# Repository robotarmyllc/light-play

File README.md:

# light-play
All files related to the Light Play (2013) delta robot project.

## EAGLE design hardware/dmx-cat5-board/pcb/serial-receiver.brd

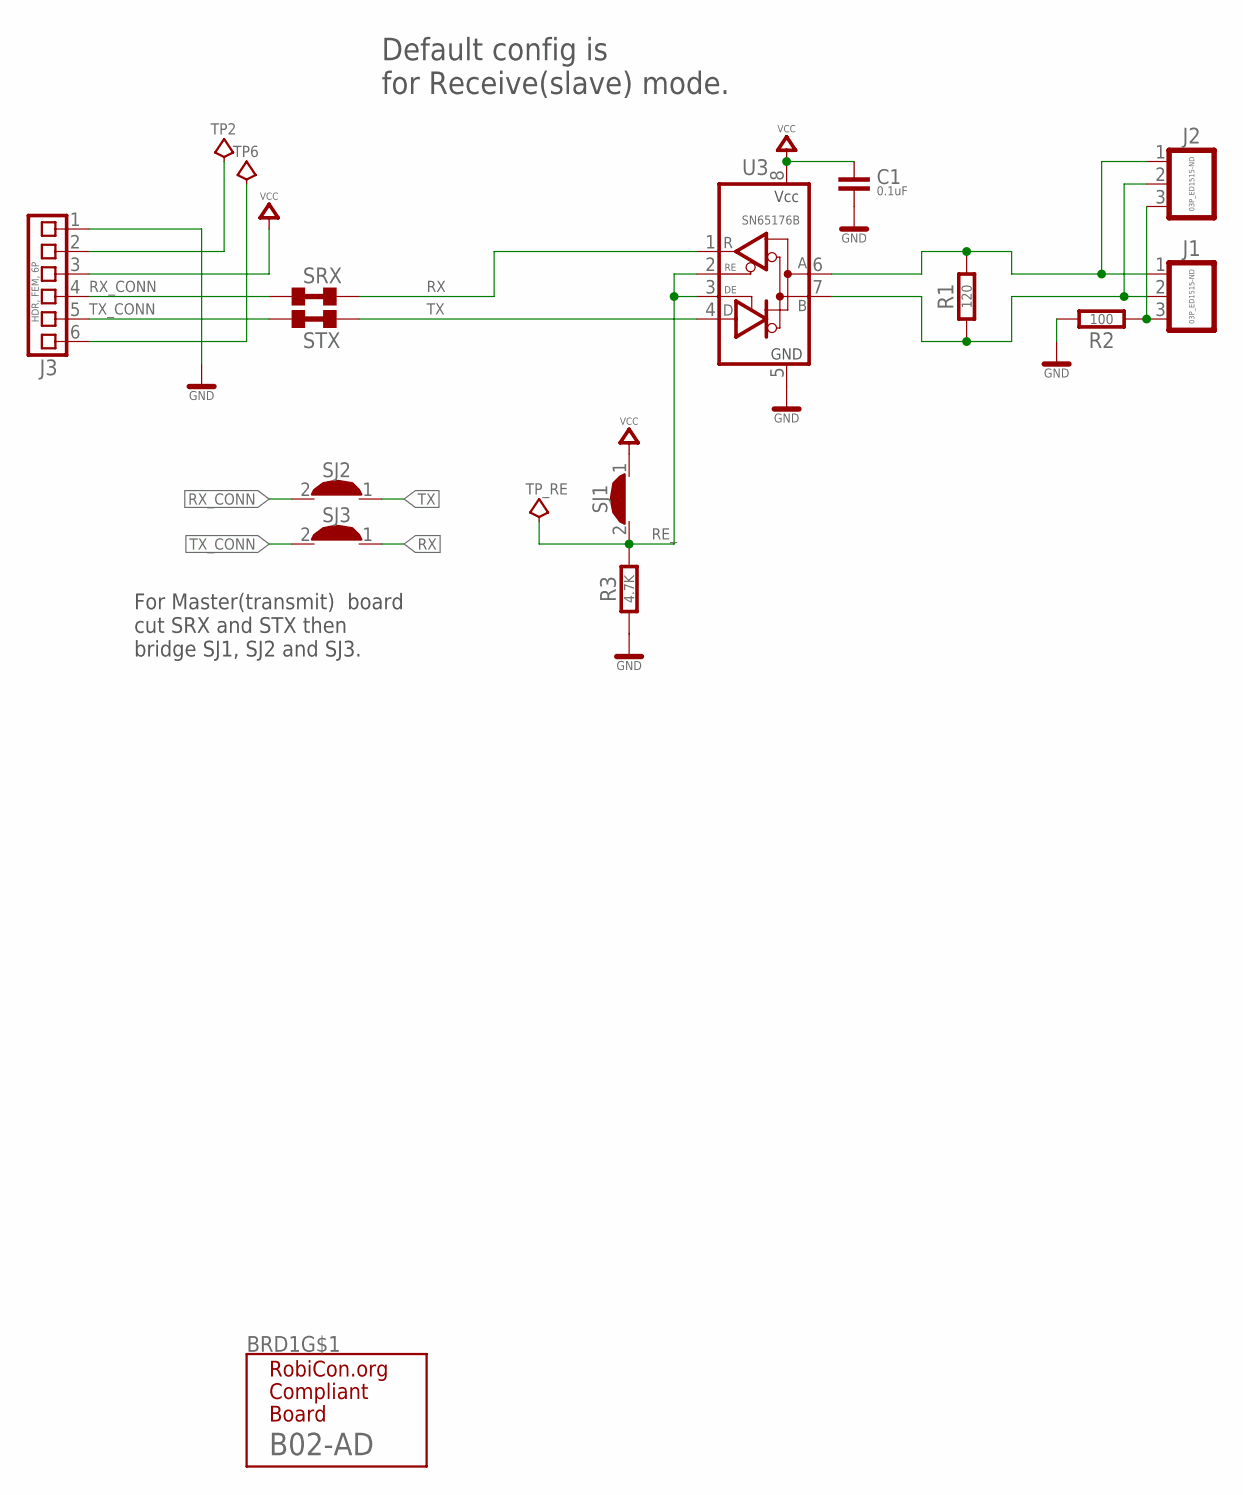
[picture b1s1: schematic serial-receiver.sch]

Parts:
BRD1: B02-AD
C1: 0.1uF; 0603
J1, J2: 03P_ED1515-ND; TB35-03
J3: HDR, FEM, 6P; FE06
R1: 120; 1206
R2: 100; 1206
R3: 4.7K; 0603
SJ1, SJ2, SJ3: SOLDER_JUMPER; SOLDER_JUMP
SRX: SHORT0603; 0603-SHORT
STX: SHORT0603; 0603-SHORT
TP2, TP6: TEST_POINT_SM_2X2; TP-SMT-020X020
TP_RE: TEST_POINT_SM_2X2; TP-SMT-020X020
U3: SN65176B; SOP08

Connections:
A: J1.1, J2.1, R1.2, U3.6 (A)
B: J1.2, J2.2, R1.1, U3.7 (B)
C: J1.3, J2.3, R2.2
GND: BRD1.A, BRD1.D, C1.2, J3.1, R2.1, R3.1, U3.5 (GND)
unnamed: J3.2, TP2.1
unnamed: J3.6, TP6.1
RE_: R3.2, SJ1.2, TP_RE.1, U3.2 (RE), U3.3 (DE)
RX: SJ3.1, SRX.2, U3.1 (R)
RX_CONN: J3.4, SJ2.2, SRX.1
TX: SJ2.1, STX.2, U3.4 (D)
TX_CONN: J3.5, SJ3.2, STX.1
VCC: C1.1, J3.3, SJ1.1, U3.8 (VCC)

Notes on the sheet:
Default config is for Receive(slave) mode.
For Master(transmit) board cut SRX and STX then bridge SJ1, SJ2 and SJ3.

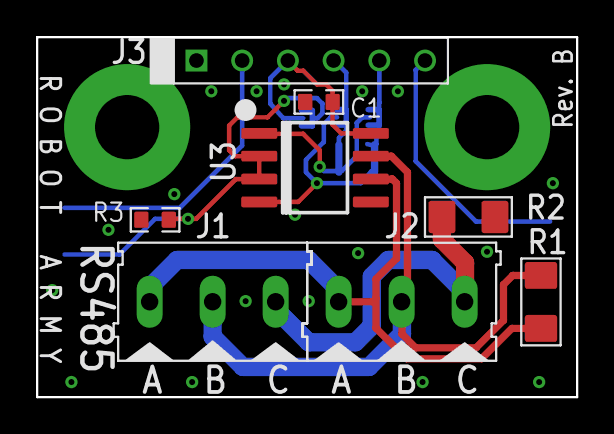
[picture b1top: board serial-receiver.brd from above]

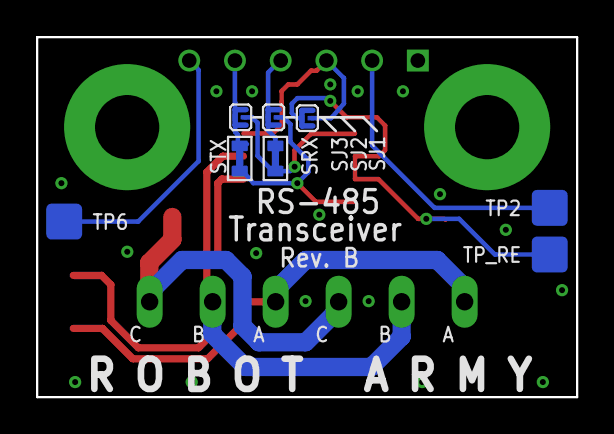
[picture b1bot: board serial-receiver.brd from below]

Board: 2 copper layers, 30.0 x 20.0 mm, 17 parts (8 on the bottom side), 12 nets.

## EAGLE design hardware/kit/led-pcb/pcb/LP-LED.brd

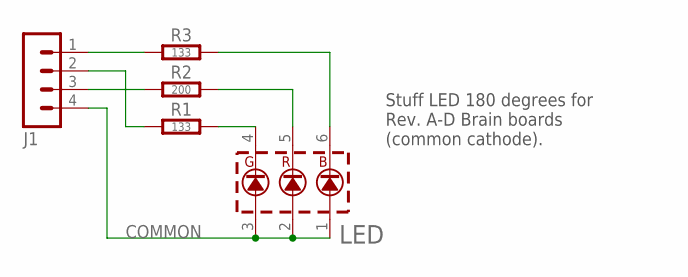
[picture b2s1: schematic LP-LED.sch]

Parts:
J1: MA04-1
LED: RGB_INDIVPLCC-6; PLCC-6
R1, R3: 133; 0805
R2: 200; 0805

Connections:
COMMON: J1.4, LED.1 (AB), LED.2 (AR), LED.3 (AG)
unnamed: LED.4 (KG), R1.2
unnamed: J1.3, R2.1
unnamed: LED.6 (KB), R3.2
unnamed: LED.5 (KR), R2.2
unnamed: J1.2, R1.1
unnamed: J1.1, R3.1

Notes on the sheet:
Stuff LED 180 degrees for Rev. A-D Brain boards (common cathode).

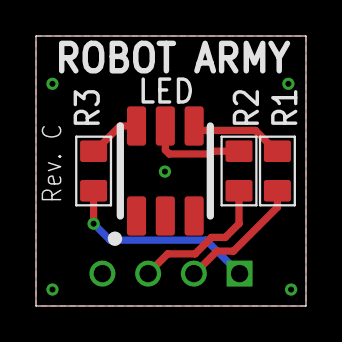
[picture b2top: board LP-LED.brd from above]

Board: 2 copper layers, 15.0 x 15.0 mm, 5 parts (1 on the bottom side), 7 nets.

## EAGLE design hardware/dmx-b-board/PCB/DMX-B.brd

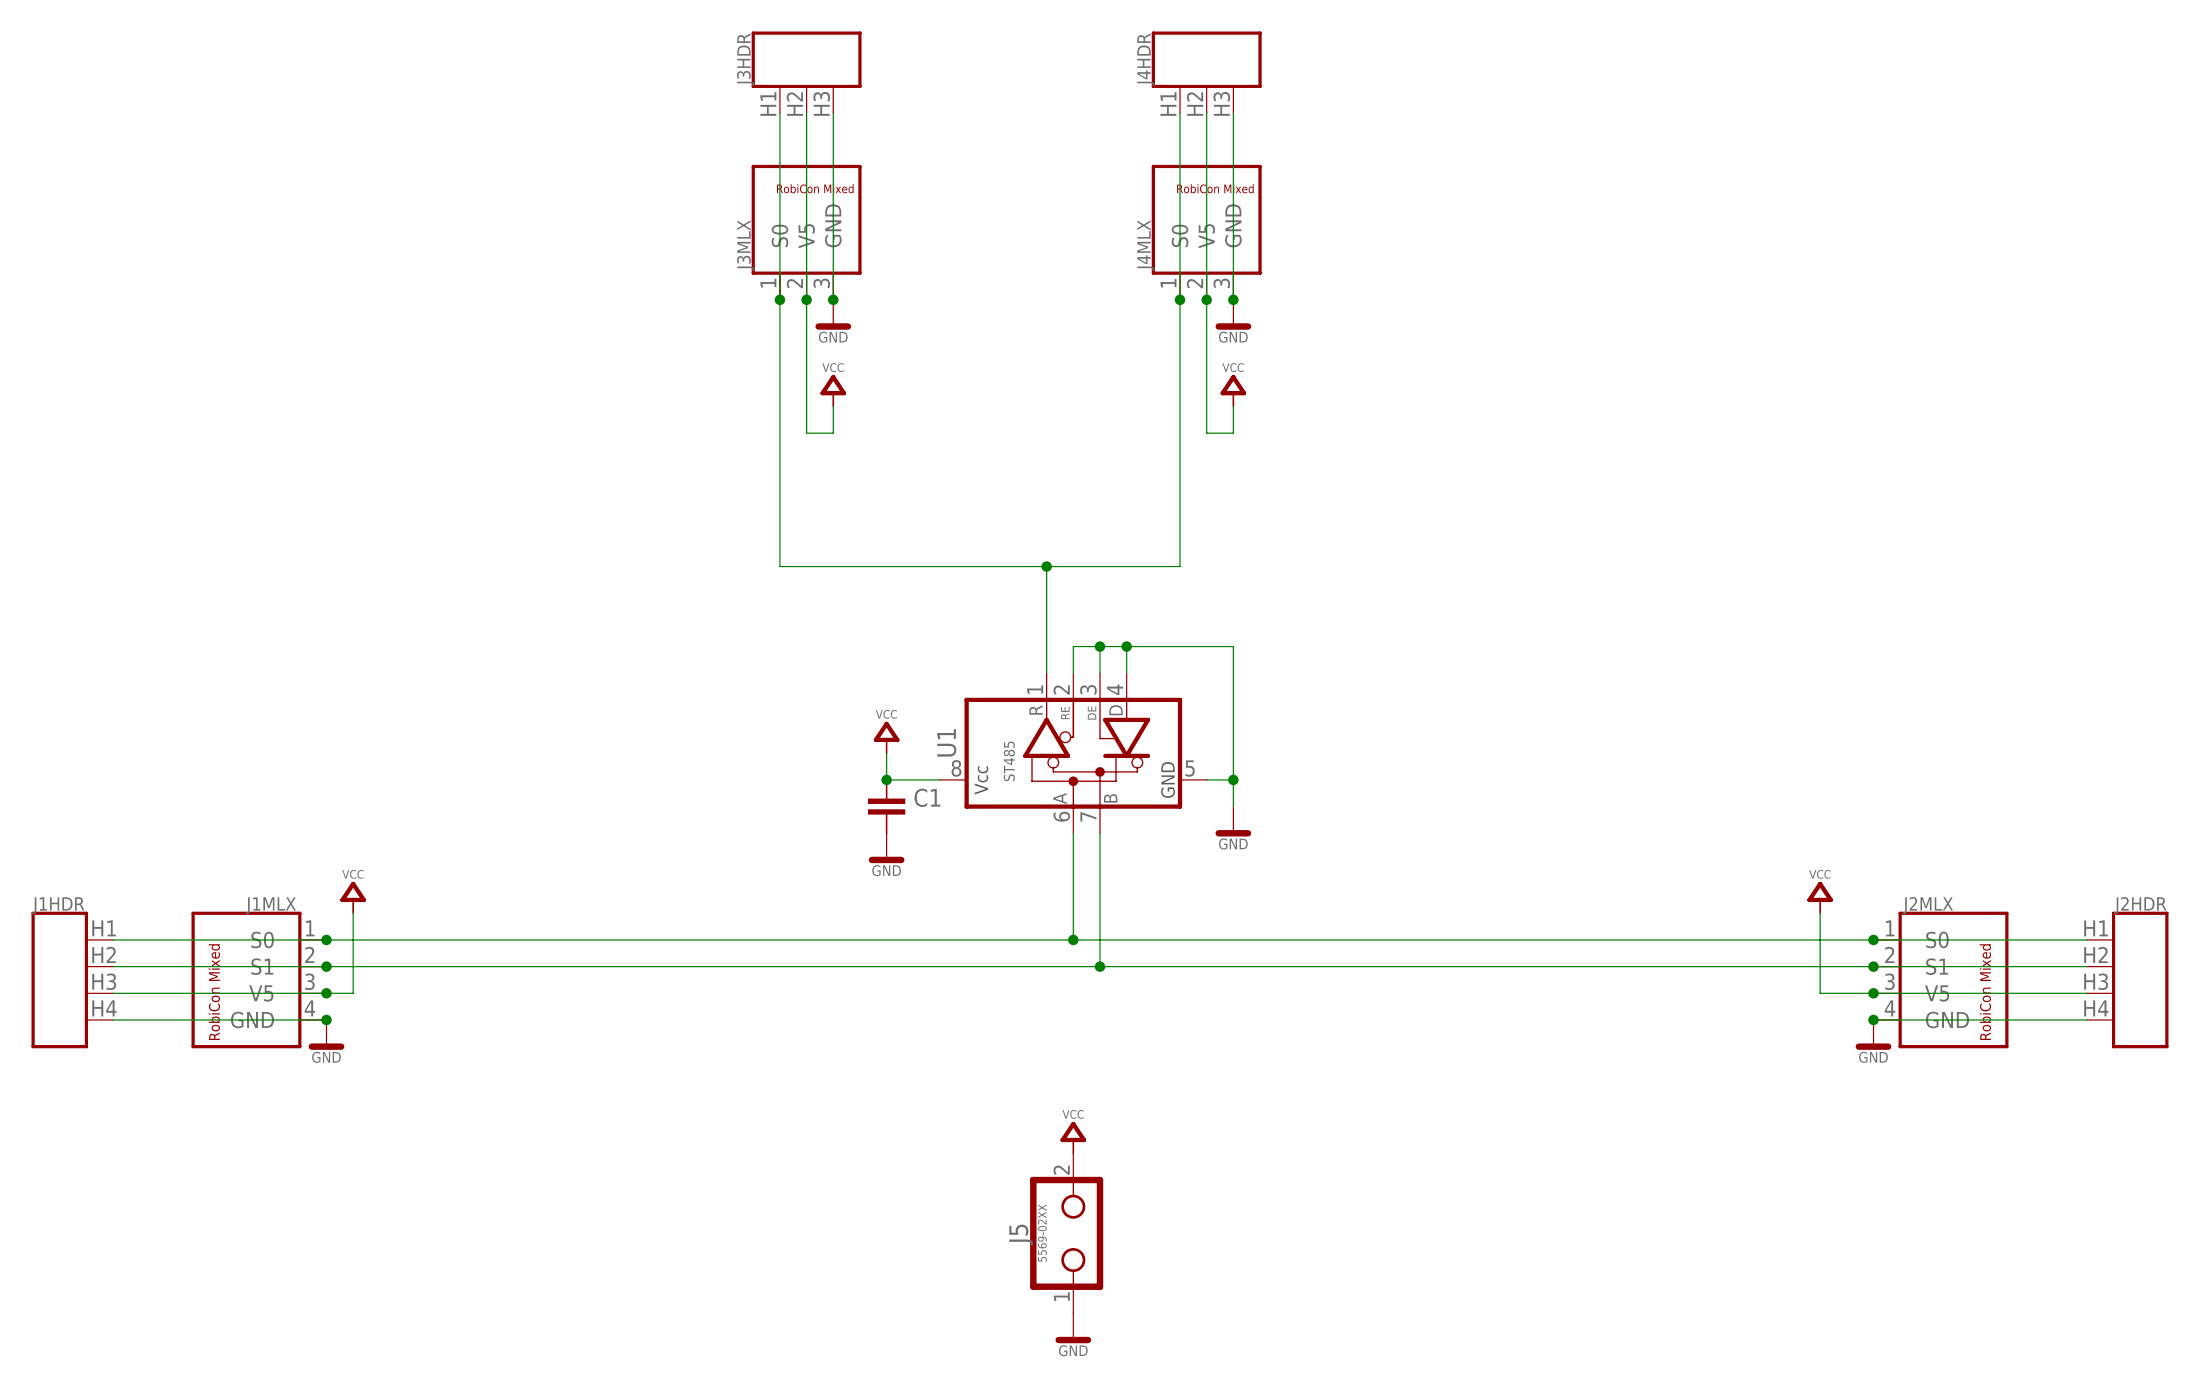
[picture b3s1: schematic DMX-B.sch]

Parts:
C1: CAPACITOR0603; 0603
J1, J2: ROBICON_M_04P_DUAL; ROBICON-DUAL-04P
J3, J4: ROBICON_M_03P_DUAL; ROBICON-DUAL-03P
J5: 5569-02XX; MOLEX-5569-02XX
U1: ST485; SOP08

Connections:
GND: C1.2, J1.4 (GND), J1.H4 (4), J2.4 (GND), J2.H4 (4), J3.3 (GND), J3.H3 (3), J4.3 (GND), J4.H3 (3), J5.1, U1.2 (RE), U1.3 (DE), U1.4 (D), U1.5 (GND)
unnamed: J1.1 (S0), J1.H1 (1), J2.1 (S0), J2.H1 (1), U1.6 (A)
unnamed: J1.2 (S1), J1.H2 (2), J2.2 (S1), J2.H2 (2), U1.7 (B)
unnamed: J3.1 (S0), J3.H1 (1), J4.1 (S0), J4.H1 (1), U1.1 (R)
VCC: C1.1, J1.3 (V5), J1.H3 (3), J2.3 (V5), J2.H3 (3), J3.2 (V5), J3.H2 (2), J4.2 (V5), J4.H2 (2), J5.2, U1.8 (VCC)

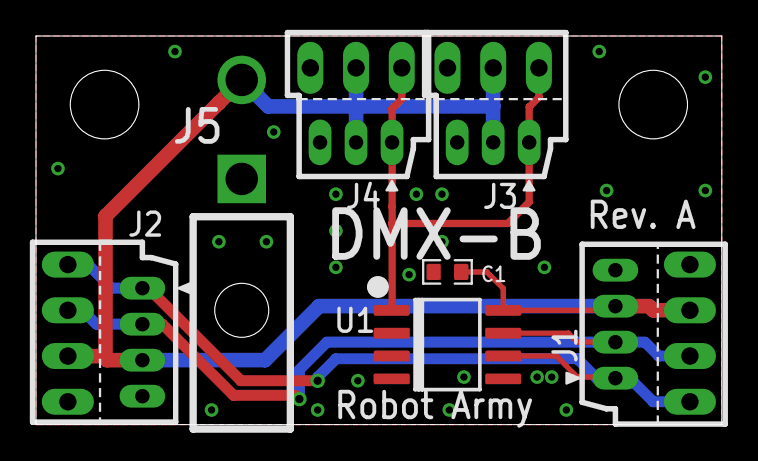
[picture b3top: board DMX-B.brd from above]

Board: 2 copper layers, 38.1 x 21.6 mm, 7 parts (0 on the bottom side), 5 nets.

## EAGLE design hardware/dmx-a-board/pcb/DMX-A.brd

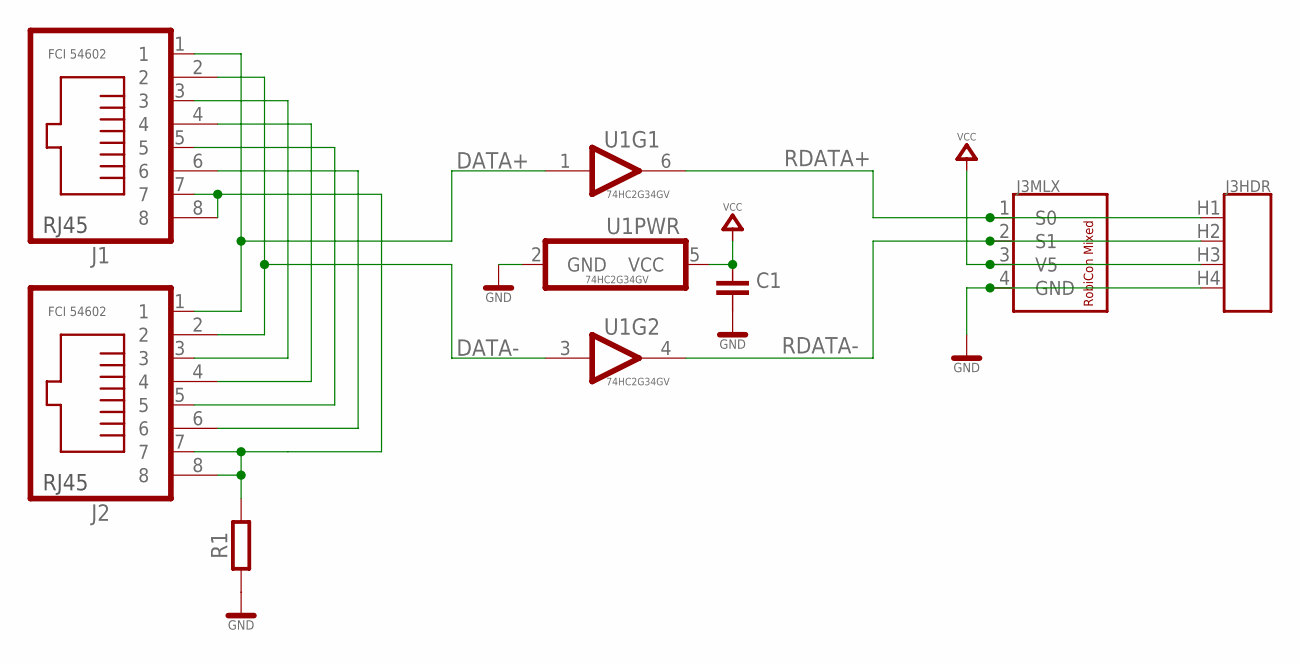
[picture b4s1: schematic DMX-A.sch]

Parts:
C1: CAPACITOR0603; 0603
J1, J2: FCI 54602; FCI_54602
J3: ROBICON_M_04P_DUAL; ROBICON-DUAL-04P
R1: RESISTOR1206; 1206
U1: 74HC2G34GV; TSOP-6

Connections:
DATA+: J1.1, J2.1, U1.1 (A)
DATA-: J1.2, J2.2, U1.3 (A)
GND: C1.2, J3.4 (GND), J3.H4 (4), R1.1, U1.2 (GND)
unnamed: J1.3, J2.3
unnamed: J1.4, J2.4
unnamed: J1.5, J2.5
unnamed: J1.6, J2.6
RDATA+: J3.1 (S0), J3.H1 (1), U1.6 (Y)
RDATA-: J3.2 (S1), J3.H2 (2), U1.4 (Y)
RJ_GND: J1.7, J1.8, J2.7, J2.8, R1.2
VCC: C1.1, J3.3 (V5), J3.H3 (3), U1.5 (VCC)

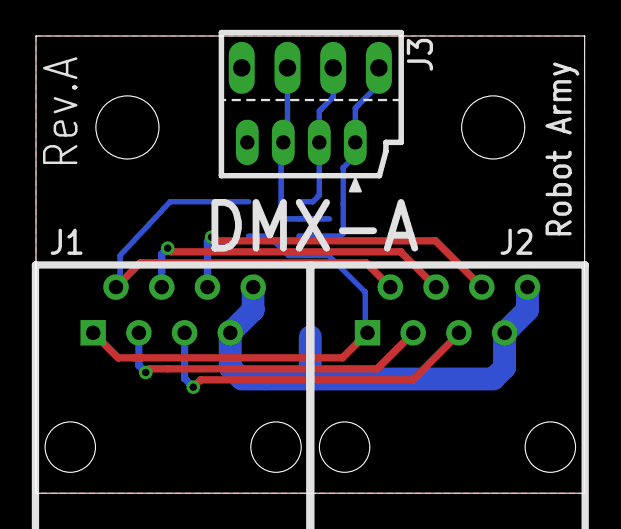
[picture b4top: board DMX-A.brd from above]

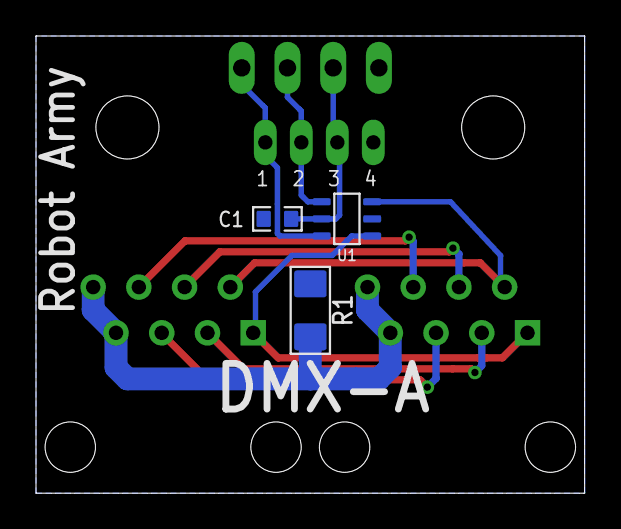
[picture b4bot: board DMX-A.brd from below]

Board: 2 copper layers, 30.5 x 25.4 mm, 6 parts (3 on the bottom side), 11 nets.

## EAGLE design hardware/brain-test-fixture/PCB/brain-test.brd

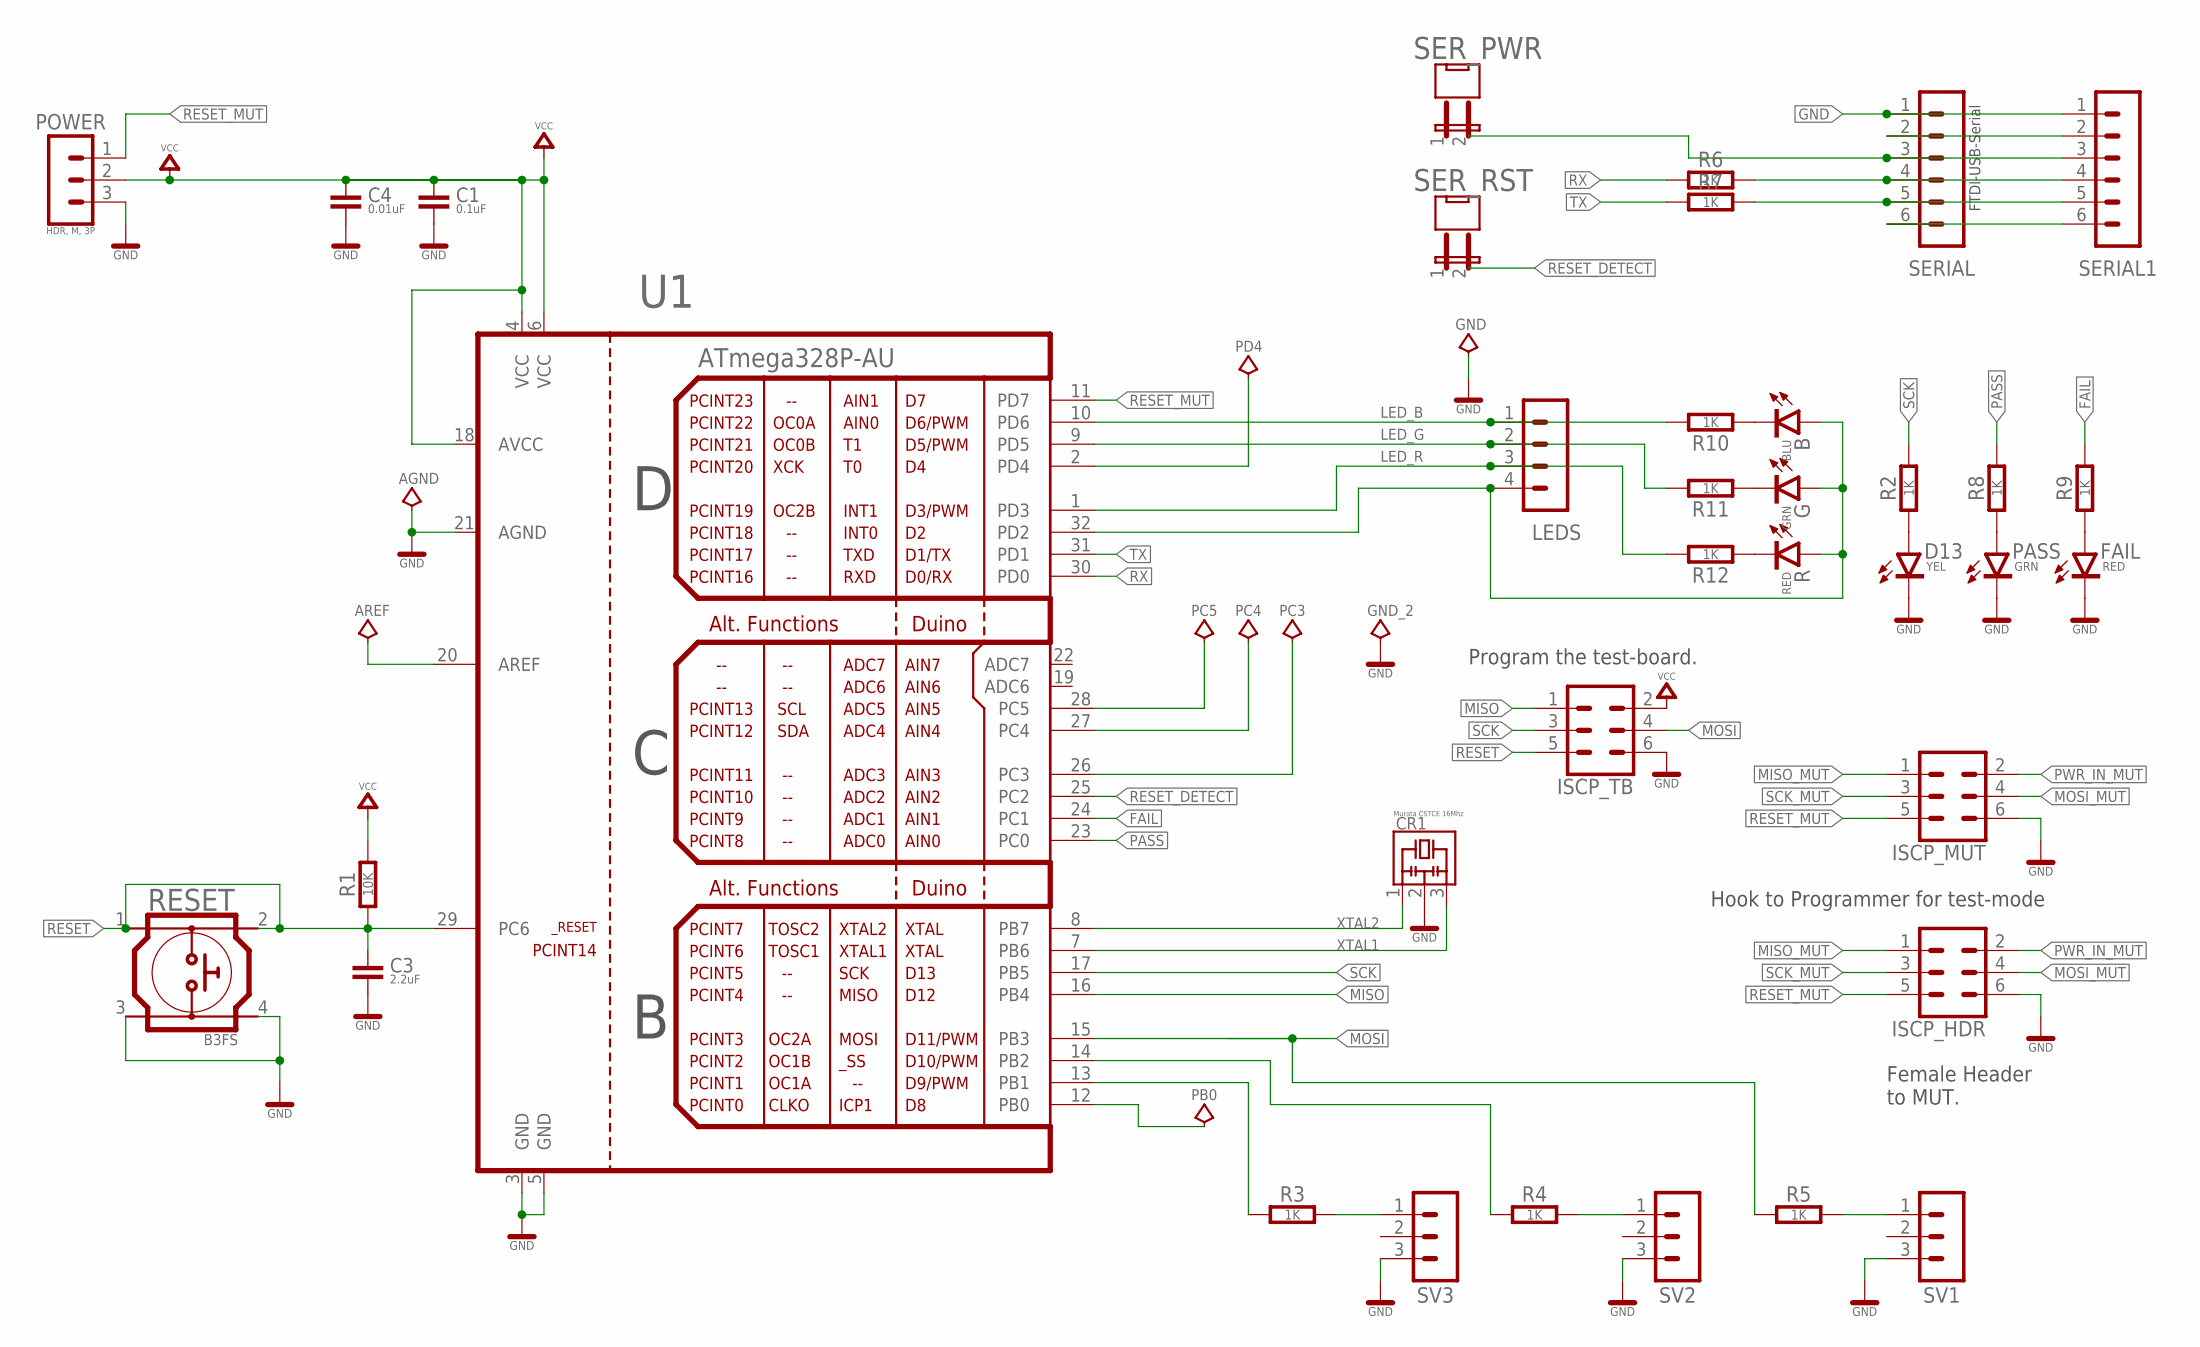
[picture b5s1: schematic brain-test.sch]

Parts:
AGND: TEST_POINT_SM_2X2; TP-SMT-020X020
AREF: TEST_POINT_SM_2X2; TP-SMT-020X020
B: BLU; SMD_0603
C1: 0.1uF; 0603
C3: 2.2uF; 0603
C4: 0.01uF; 0603
CR1: Murata CSTCE 16Mhz; MURATA_CSTCE
D13: YEL; SMD_0603
FAIL: RED; SMD_0603
G: GRN; SMD_0603
GND: TEST_POINT_SM_2X2; TP-SMT-020X020
GND_2: TEST_POINT_SM_2X2; TP-SMT-020X020
ISCP_HDR: MA03-2
ISCP_MUT: MA03-2
ISCP_TB: MA03-2
LEDS: MA04-1
PASS: GRN; SMD_0603
PB0: TEST_POINT_SM_2X2; TP-SMT-020X020
PC3, PC4, PC5: TEST_POINT_SM_2X2; TP-SMT-020X020
PD4: TEST_POINT_SM_2X2; TP-SMT-020X020
POWER: HDR, M, 3P; MA03-1
R: RED; SMD_0603
R1: 10K; 0603
R2, R3, R4, R5, R6, R7, R8, R9, R10, R11, R12: 1K; 0603
RESET: B3FS
SERIAL, SERIAL1: MA06-1
SER_PWR: JMP01VT; MA02-1-FAT
SER_RST: JMP01VT; MA02-1-FAT
SV1, SV2, SV3: MA03-1
U1: ATmega328P-AU; TQFP-32-08

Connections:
AREF: AREF.1, U1.20 (AREF)
CTS: SERIAL.2, SERIAL1.2
FAIL: R9.2, U1.24 (PC1)
GND: AGND.1, C1.2, C3.2, C4.2, CR1.2, D13.K (C), FAIL.K (C), GND.1, GND_2.1, ISCP_HDR.6, ISCP_MUT.6, ISCP_TB.6, PASS.K (C), POWER.3, RESET.3, RESET.4, SERIAL.1, SERIAL1.1, SV1.3, SV2.3, SV3.3, U1.3 (GND), U1.5 (GND), U1.21 (AGND)
LED_B: LEDS.1, R10.2, U1.10 (PD6)
LED_G: LEDS.2, R11.2, U1.9 (PD5)
LED_R: LEDS.3, R12.2, U1.1 (PD3)
MISO: ISCP_TB.1, U1.16 (PB4)
MISO_MUT: ISCP_HDR.1, ISCP_MUT.1
MOSI: ISCP_TB.4, R5.1, U1.15 (PB3)
MOSI_MUT: ISCP_HDR.4, ISCP_MUT.4
unnamed: D13.A, R2.1
unnamed: PASS.A, R8.1
unnamed: PD4.1, U1.2 (PD4)
unnamed: PC5.1, U1.28 (PC5)
unnamed: R3.2, SV3.1
unnamed: FAIL.A, R9.1
unnamed: PC4.1, U1.27 (PC4)
unnamed: PC3.1, U1.26 (PC3)
unnamed: R4.2, SV2.1
unnamed: R5.2, SV1.1
unnamed: B.K (C), R10.1
unnamed: G.K (C), R11.1
unnamed: R.K (C), R12.1
unnamed: R4.1, U1.14 (PB2)
unnamed: R3.1, U1.13 (PB1)
PASS: R8.2, U1.23 (PC0)
PWR_IN: B.A, G.A, LEDS.4, R.A, U1.32 (PD2)
PWR_IN_MUT: ISCP_HDR.2, ISCP_MUT.2
RESET: C3.1, ISCP_TB.5, R1.1, RESET.1, RESET.2, U1.29 (PC6)
RESET_DETECT: SER_RST.2, U1.25 (PC2)
RESET_MUT: ISCP_HDR.5, ISCP_MUT.5, POWER.1, U1.11 (PD7)
RTS: SERIAL.6, SERIAL1.6
RX: R6.1, U1.30 (PD0)
RXD: R7.2, SERIAL.5, SERIAL1.5
SCK: ISCP_TB.3, R2.2, U1.17 (PB5)
SCK_MUT: ISCP_HDR.3, ISCP_MUT.3
SERVO_EN: PB0.1, U1.12 (PB0)
TX: R7.1, U1.31 (PD1)
TXD: R6.2, SERIAL.4, SERIAL1.4
VCC: C1.1, C4.1, ISCP_TB.2, POWER.2, R1.2, U1.4 (VCC), U1.6 (VCC), U1.18 (AVCC)
VCC5: SERIAL.3, SERIAL1.3, SER_PWR.2
XTAL1: CR1.3, U1.7 (PB6)
XTAL2: CR1.1, U1.8 (PB7)

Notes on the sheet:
FTDI-USB-Serial
Hook to Programmer for test-mode
Program the test-board.
Female Header to MUT.

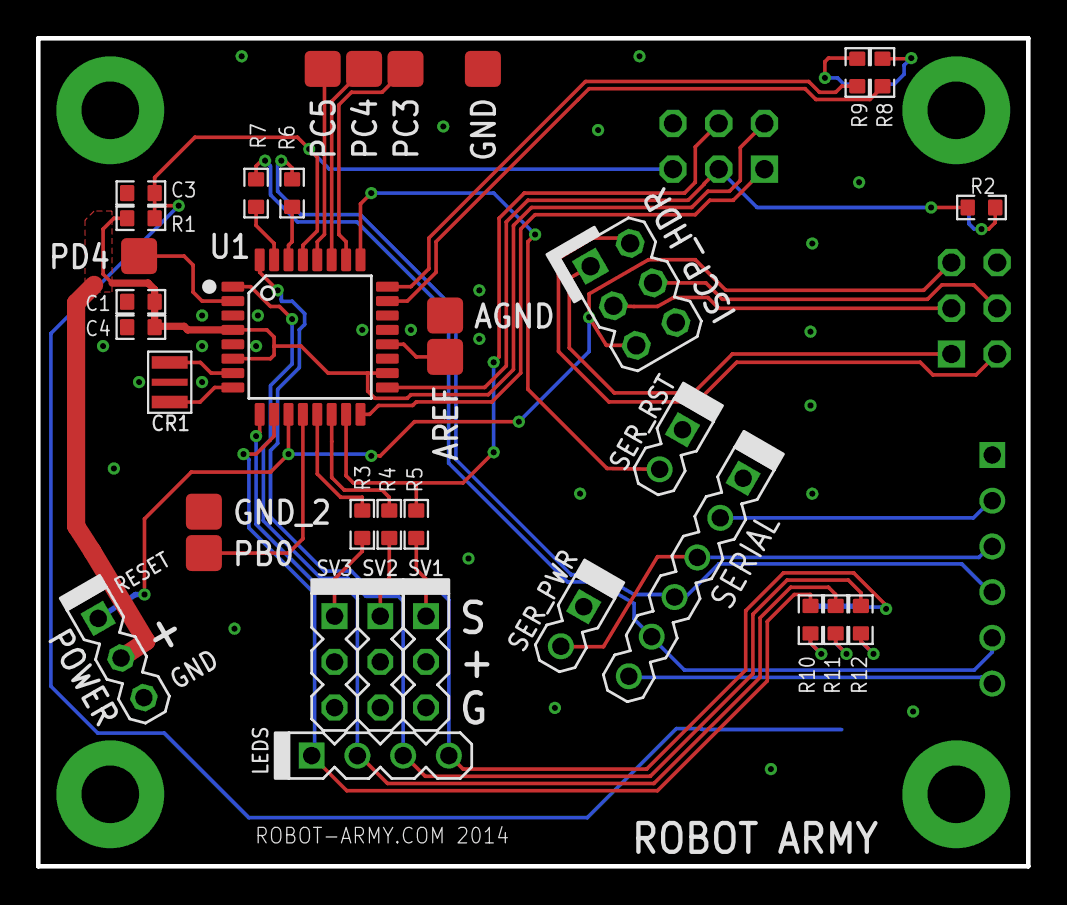
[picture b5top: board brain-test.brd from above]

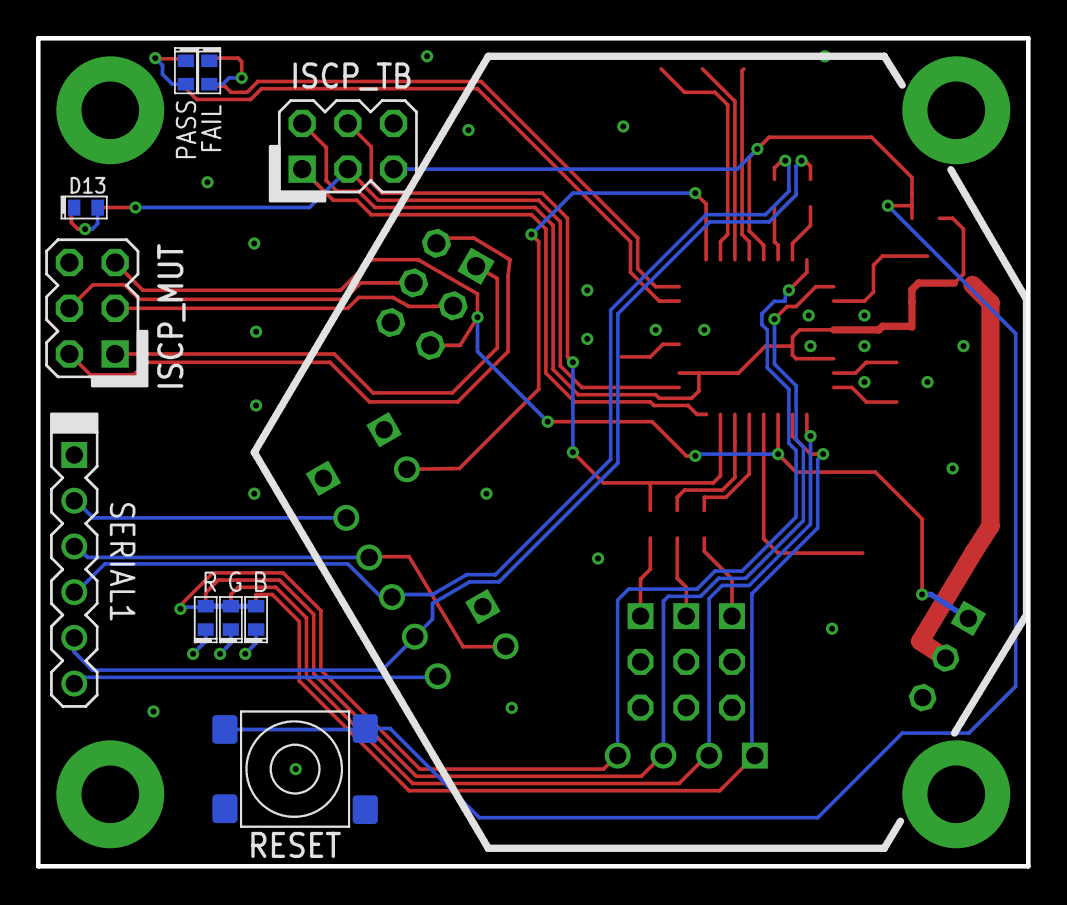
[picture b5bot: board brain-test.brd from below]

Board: 2 copper layers, 55.0 x 46.0 mm, 45 parts (10 on the bottom side), 44 nets.

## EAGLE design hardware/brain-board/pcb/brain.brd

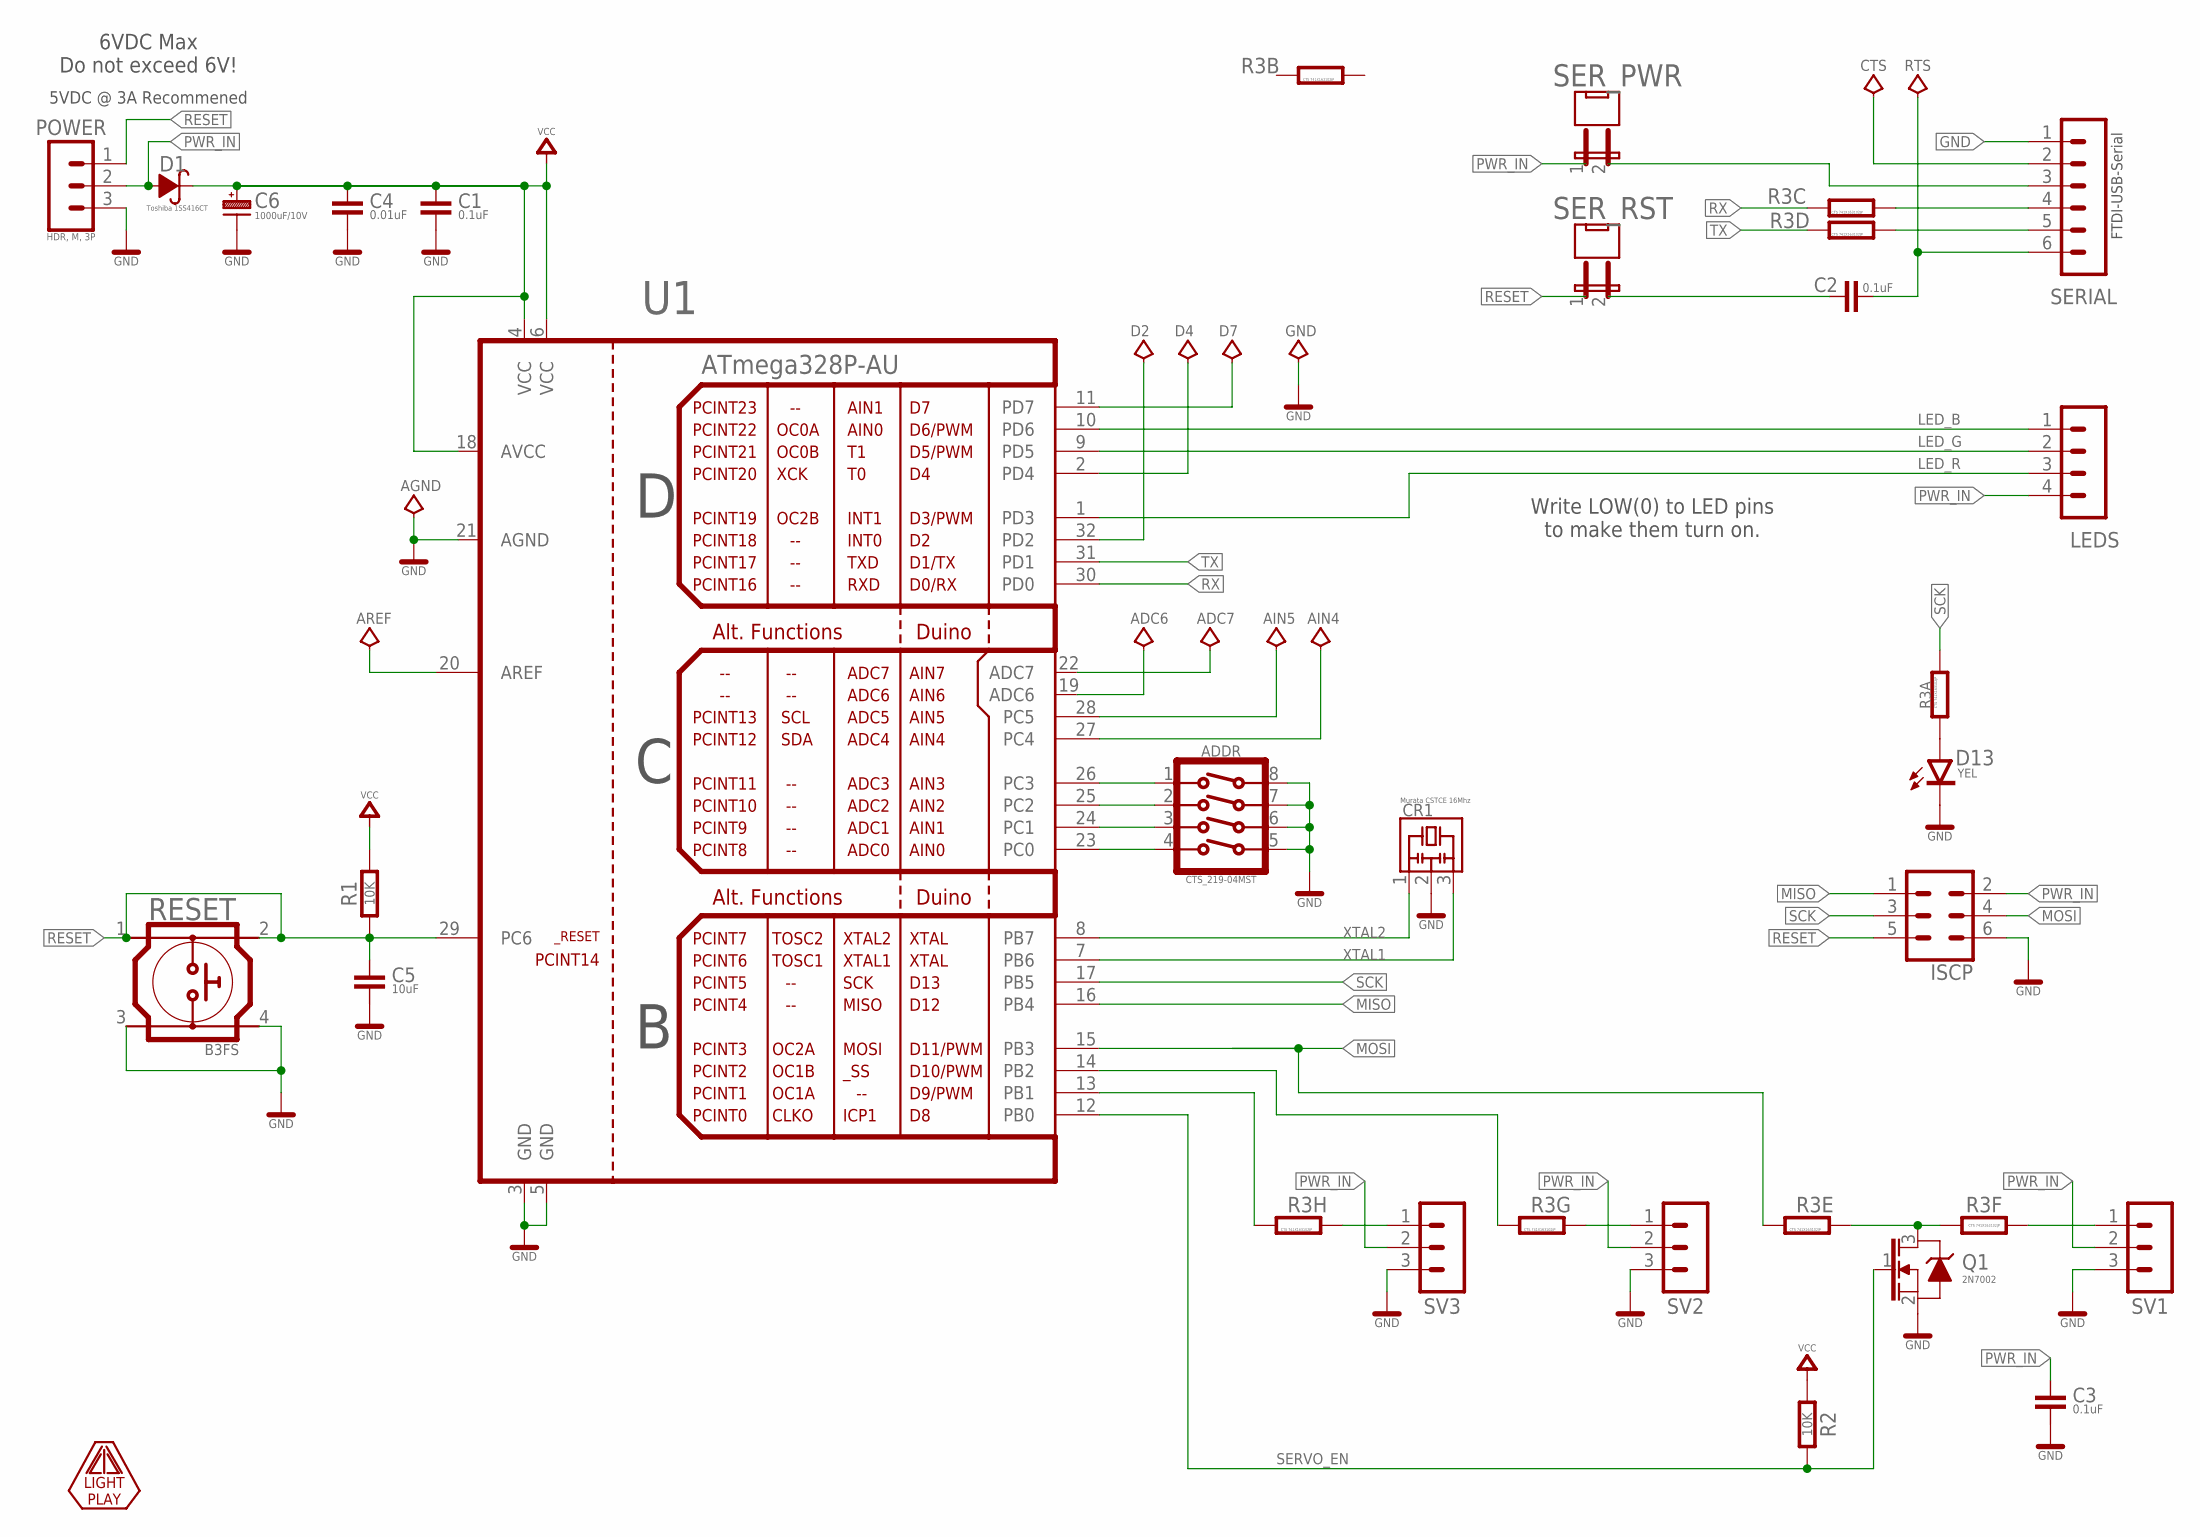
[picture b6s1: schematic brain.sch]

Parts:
ADC6, ADC7: TEST_POINT_SM_2X2; TP-SMT-020X020
ADDR: CTS_219-04MST; CTS_4P_GULLWING
AGND: TEST_POINT_SM_2X2; TP-SMT-020X020
AIN4, AIN5: TEST_POINT_SM_2X2; TP-SMT-020X020
AREF: TEST_POINT_SM_2X2; TP-SMT-020X020
C1, C2, C3: 0.1uF; 0603
C4: 0.01uF; 0603
C5: 10uF; 0805
C6: 1000uF/10V; CAP_ALUM_THD_8
CR1: Murata CSTCE 16Mhz; MURATA_CSTCE
CTS: TEST_POINT_SM_2X2; TP-SMT-020X020
D1: Toshiba 1SS416CT; CST2
D2, D4, D7: TEST_POINT_SM_2X2; TP-SMT-020X020
D13: YEL; SMD_0603
GND: TEST_POINT_SM_2X2; TP-SMT-020X020
ISCP: MA03-2
LEDS: MA04-1
LOGO2: LIGHT_PLAY_20MM; LIGHTPLAY_20MM
POWER: HDR, M, 3P; MA03-1
Q1: 2N7002; SOT-23
R1, R2: 10K; 0603
R3: CTS 741X163102JP; RESNET_0402_X8
RESET: B3FS
RTS: TEST_POINT_SM_2X2; TP-SMT-020X020
SERIAL: MA06-1
SER_PWR: JMP01VT; MA02-1-FAT
SER_RST: JMP01VT; MA02-1-FAT
SV1, SV2, SV3: MA03-1
U1: ATmega328P-AU; TQFP-32-08

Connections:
AREF: AREF.1, U1.20 (AREF)
CTS: CTS.1, SERIAL.2
GND: ADDR.5, ADDR.6, ADDR.7, ADDR.8, AGND.1, C1.2, C3.2, C4.2, C5.2, C6.N, CR1.2, D13.K (C), GND.1, ISCP.6, POWER.3, Q1.2 (S), RESET.3, RESET.4, SERIAL.1, SV1.3, SV2.3, SV3.3, U1.3 (GND), U1.5 (GND), U1.21 (AGND)
LED_B: LEDS.1, U1.10 (PD6)
LED_G: LEDS.2, U1.9 (PD5)
LED_R: LEDS.3, U1.1 (PD3)
MISO: ISCP.1, U1.16 (PB4)
MOSI: ISCP.4, R3.5 (1), U1.15 (PB3)
unnamed: D2.1, U1.32 (PD2)
unnamed: R3.6 (1), SV1.1
unnamed: D4.1, U1.2 (PD4)
unnamed: ADDR.1, U1.26 (PC3)
unnamed: R3.9 (2), SV3.1
unnamed: D7.1, U1.11 (PD7)
unnamed: ADC6.1, U1.19 (ADC6)
unnamed: ADC7.1, U1.22 (ADC7)
unnamed: R3.10 (2), SV2.1
unnamed: Q1.3 (D), R3.11 (2), R3.12 (2)
unnamed: AIN5.1, U1.28 (PC5)
unnamed: AIN4.1, U1.27 (PC4)
unnamed: C2.1, SER_RST.2
unnamed: D13.A, R3.16 (2)
unnamed: R3.7 (1), U1.14 (PB2)
unnamed: R3.8 (1), U1.13 (PB1)
unnamed: ADDR.2, U1.25 (PC2)
unnamed: ADDR.3, U1.24 (PC1)
unnamed: ADDR.4, U1.23 (PC0)
PWR_IN: C3.1, D1.A, ISCP.2, LEDS.4, POWER.2, SER_PWR.1, SV1.2, SV2.2, SV3.2
RESET: C5.1, ISCP.5, POWER.1, R1.1, RESET.1, RESET.2, SER_RST.1, U1.29 (PC6)
RTS: C2.2, RTS.1, SERIAL.6
RX: R3.3 (1), U1.30 (PD0)
RXD: R3.13 (2), SERIAL.5
SCK: ISCP.3, R3.1, U1.17 (PB5)
SERVO_EN: Q1.1 (G), R2.2, U1.12 (PB0)
TX: R3.4 (1), U1.31 (PD1)
TXD: R3.14 (2), SERIAL.4
VCC: C1.1, C4.1, C6.P, D1.K, R1.2, R2.1, U1.4 (VCC), U1.6 (VCC), U1.18 (AVCC)
VCC5: SERIAL.3, SER_PWR.2
XTAL1: CR1.3, U1.7 (PB6)
XTAL2: CR1.1, U1.8 (PB7)

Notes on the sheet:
FTDI-USB-Serial
Write LOW(0) to LED pins to make them turn on.
6VDC Max Do not exceed 6V!
5VDC @ 3A Recommened

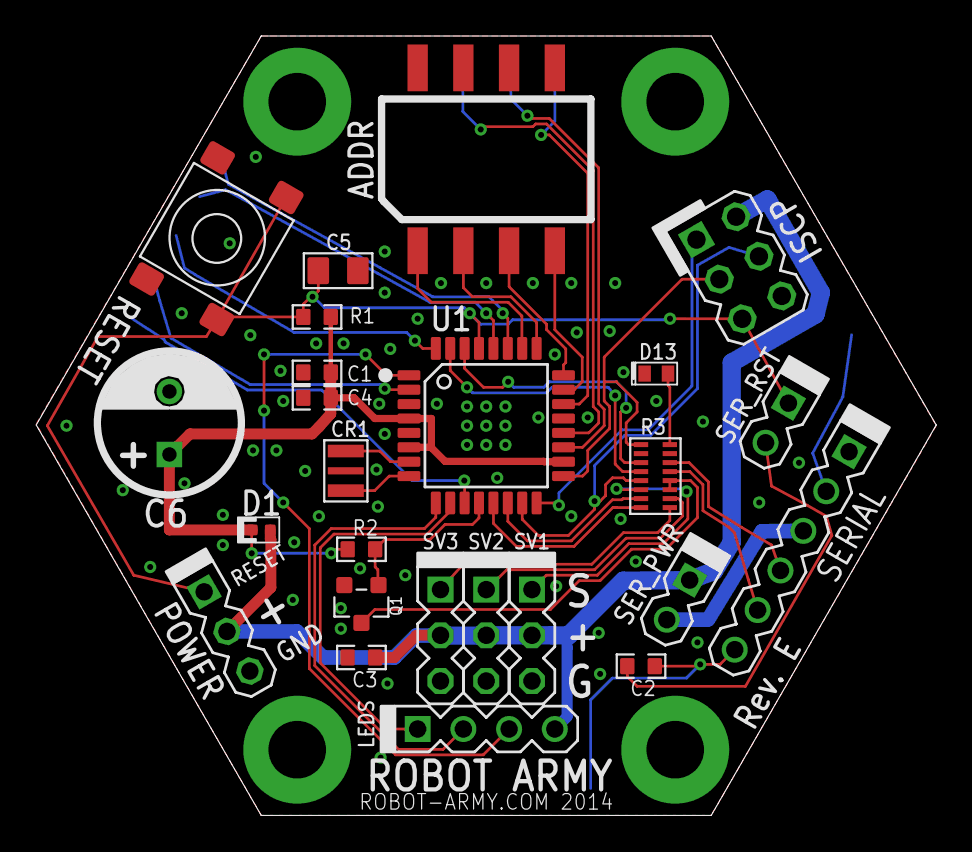
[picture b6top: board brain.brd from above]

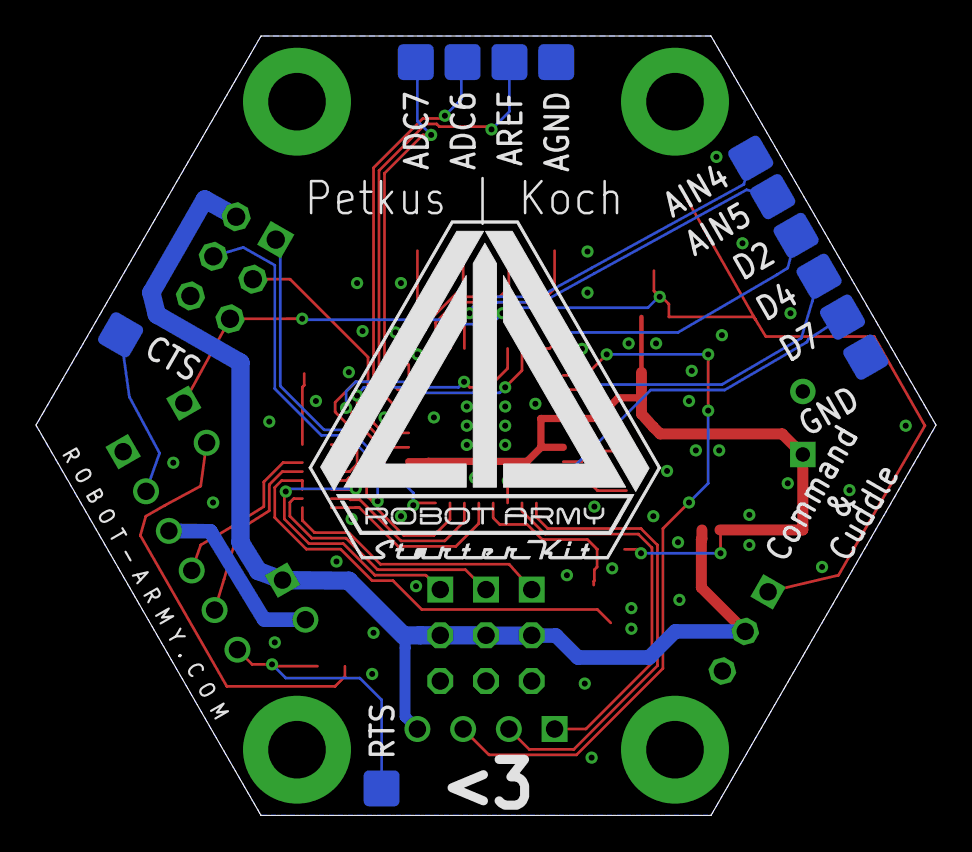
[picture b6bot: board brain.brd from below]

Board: 2 copper layers, 50.0 x 43.3 mm, 38 parts (13 on the bottom side), 40 nets.
